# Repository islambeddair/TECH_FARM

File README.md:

# TECH_FARMMoisture Sensor

General Overview:
Soil moisture sensor measure the volumetric water content in soil. Since the direct gravimetric measurement of free soil moisture requires removing, drying, and weighting of a sample, soil moisture sensors measure the volumetric water content indirectly by using some other property of the soil, such as electrical resistance, dielectric constant, or interaction with neutrons, as a proxy for the moisture content. The relation between the measured property and soil moisture must be calibrated and may vary depending on environmental factors such as soil type, temperature, or electric conductivity. Reflected microwave radiation is affected by the soil moisture and is used for remote sensing in hydrology and agriculture. Portable probe instruments can be used by farmers or gardeners.
Applications:
Agriculture:
Measuring soil moisture is important for agricultural applications to help farmers manage their irrigation systems more efficiently. Knowing the exact soil moisture conditions on their fields, not only are farmers able to generally use less water to grow a crop, they are also able to increase yields and the quality of the crop by improved management of soil moisture during critical plant growth stages.
Landscape irrigation:
In urban and suburban areas, landscapes and residential lawns are using soil moisture sensors to interface with an irrigation controller. Connecting a soil moisture sensor to a simple irrigation clock will convert it into a "smart" irrigation controller that prevents irrigation cycles when the soil is already wet, e.g. following a recent rainfall event.
Golf courses are using soil moisture sensors to increase the efficiency of their irrigation systems to prevent over-watering and leaching of fertilizers and other chemicals into the ground.
Research:
Soil moisture sensors are used in numerous research applications, e.g. in agricultural science and horticulture including irrigation planning, climate research, or environmental science including solute transport studies and as auxiliary sensors for soil respiration measurements.

	We will use moisture sensor in agricultural applications. 
Hardware Overview:
The Soil Moisture Sensor is pretty straightforward when it comes to hookup. You need to supply VCC and GND. We recommend not powering the sensor constantly to prevent oxidation of the probes (more on this in a bit). You will get a SIG out, which will be between almost VCC and GND, depending on the amount of water in the soil. The two probes are acting as a variable resistor – more water in the soil means better conductivity and results in a lower resistance and a higher SIG out. Your analog readings will vary depending on what voltage you use for Vcc as well as the resolution of your ADC pins.

First: design the moisture sensor by using EAGLE program.

•	EAGLE schematic for moisture sensor.

•	EAGLE board for moisture sensor.

Second:  made (PCB) for moisture sensor.
 
•	Moisture sensor

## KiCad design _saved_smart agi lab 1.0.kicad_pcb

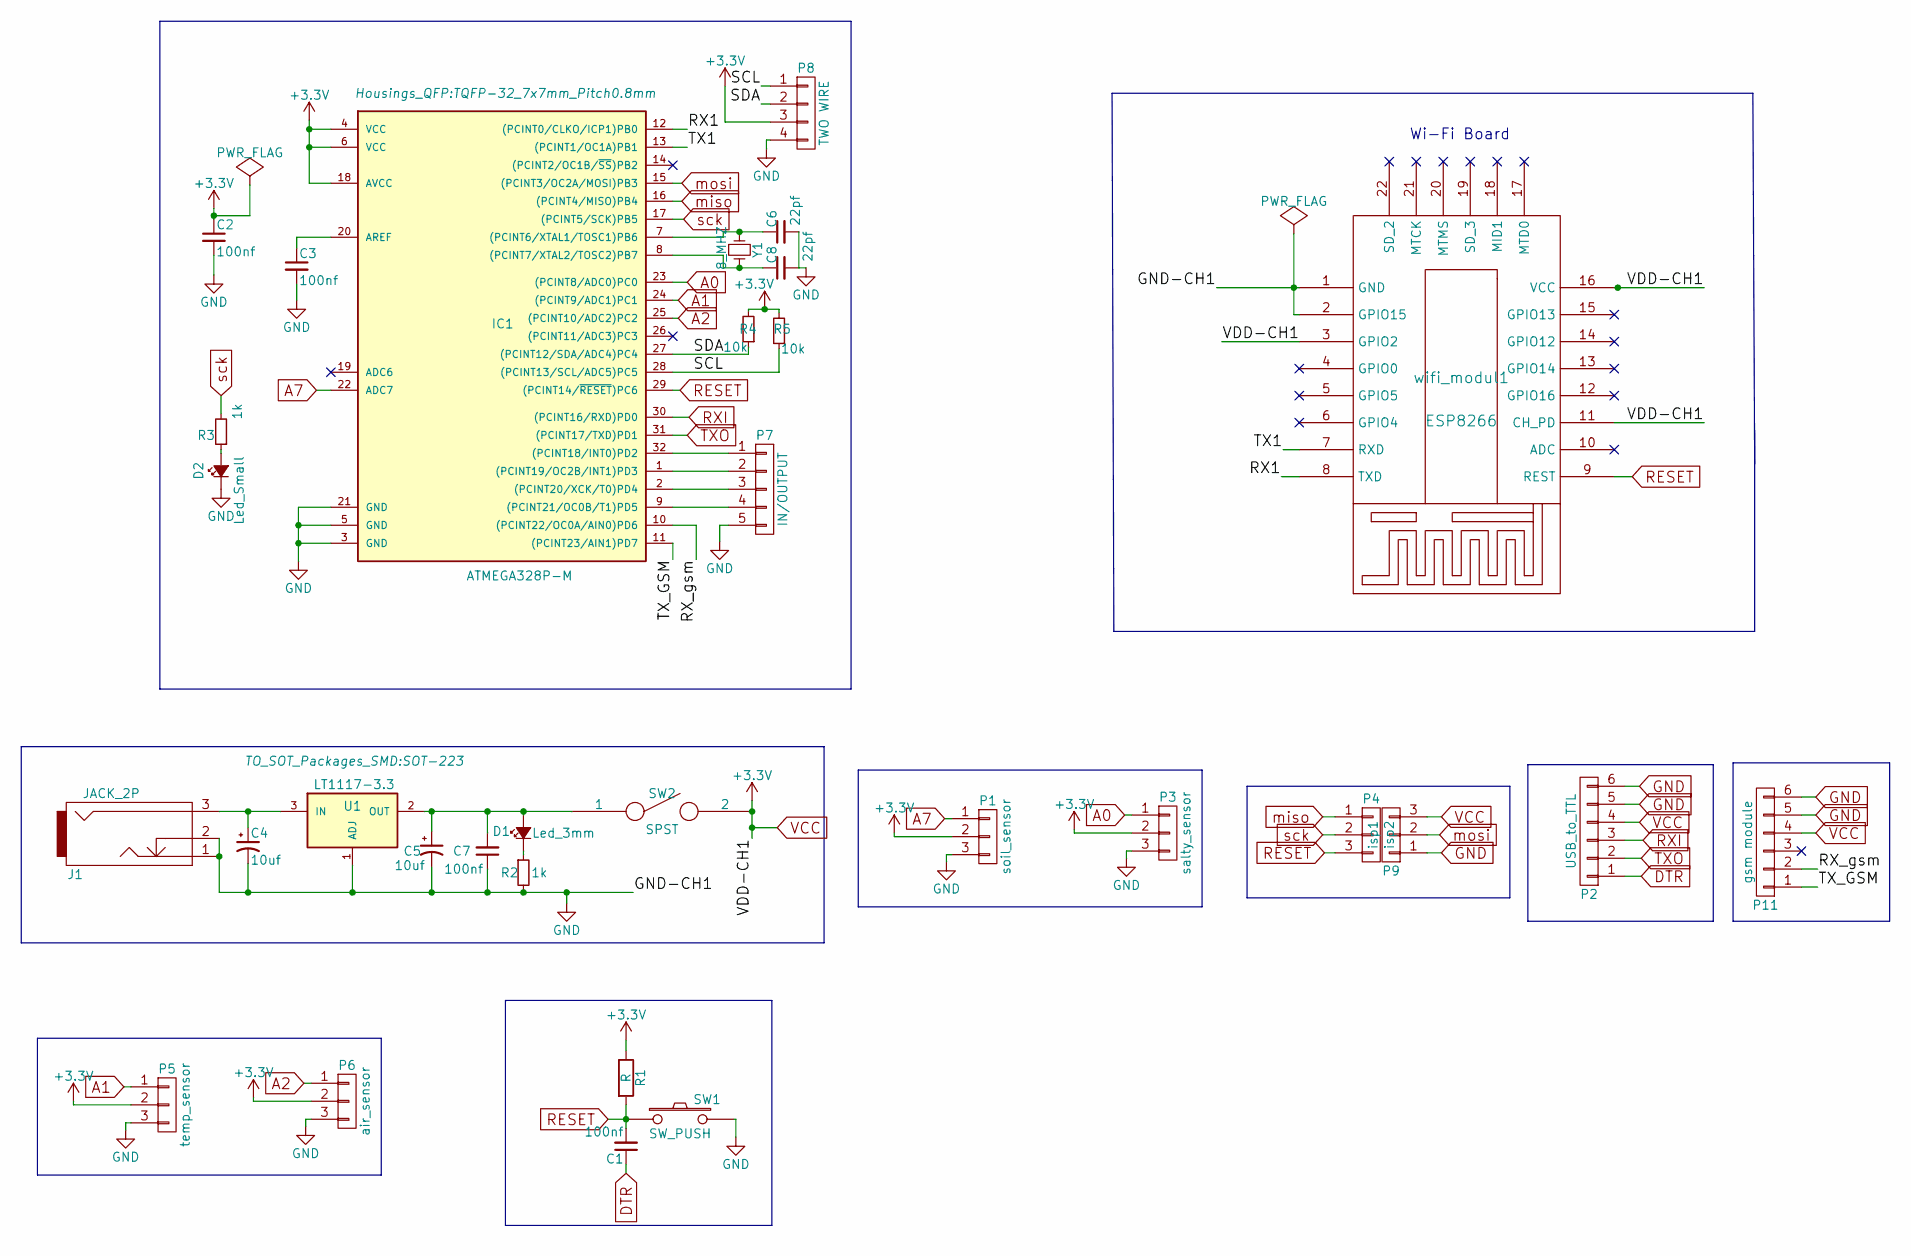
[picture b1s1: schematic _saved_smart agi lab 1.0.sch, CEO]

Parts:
C1: 100nf; C_Disc_D7.0mm_W2.5mm_P5.00mm
C2, C3, C7: 100nf; C_1206_HandSoldering
C4, C5: 10uf; C_1206_HandSoldering
C6, C8: 22pf; C_Disc_D3.0mm_W2.0mm_P2.50mm
D1: Led_3mm; LED_D3.0mm
D2: Led_Small; LED_D3.0mm
IC1: ATMEGA328P-M; TQFP-32_7x7mm_Pitch0.8mm
J1: JACK_2P; BARREL_JACK
P1: soil_sensor; AK300-3
P2: USB_to_TTL; Pin_Header_Straight_1x06_Pitch2.54mm
P3: salty_sensor; AK300-3
P4: isp2; Pin_Header_Straight_1x03_Pitch2.54mm
P5: temp_sensor; AK300-3
P6: air_sensor; AK300-3
P7: IN/OUTPUT; Pin_Header_Straight_1x05_Pitch2.54mm
P8: TWO WIRE; Pin_Header_Straight_1x04_Pitch2.54mm
P9: isp1; Pin_Header_Straight_1x03_Pitch2.54mm
P11: gsm module; Pin_Header_Straight_1x06_Pitch2.54mm
R1: R; R_1206_HandSoldering
R2, R3: 1k; R_1206_HandSoldering
R4, R5: 10k; R_1206_HandSoldering
SW1: SW_PUSH; SW_PUSH_6mm_h4.3mm
SW2: SPST; SW_PUSH_x2
U1: LT1117-3.3; SOT-223
Y1: 8_MHZ; Resonator-2pin_w7.0mm_h2.5mm
wifi_modul1: ESP8266; esp12

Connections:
/RX1: IC1.12 ((PCINT0/CLKO/ICP1)PB0), wifi_modul1.8 (TXD)
/RX_gsm: IC1.10 ((PCINT22/OC0A/AIN0)PD6), P11.2
/SCL: IC1.28 ((PCINT13/SCL/ADC5)PC5), P8.1, R5.1
/SDA: IC1.27 ((PCINT12/SDA/ADC4)PC4), P8.2, R4.1
/TX1: IC1.13 ((PCINT1/OC1A)PB1), wifi_modul1.7 (RXD)
/TX_GSM: IC1.11 ((PCINT23/AIN1)PD7), P11.1
A0: IC1.23 ((PCINT8/ADC0)PC0), P3.1
A1: IC1.24 ((PCINT9/ADC1)PC1), P5.1
A2: IC1.25 ((PCINT10/ADC2)PC2), P6.1
A7: IC1.22 (ADC7), P1.1
DTR: C1.1, P2.1
GND: C2.2, C3.2, C4.2, C5.2, C6.2, C7.1, C8.2, D2.1 (K), IC1.3 (GND), IC1.5 (GND), IC1.21 (GND), J1.1, J1.2, P1.3, P2.5, P2.6, P3.3, P5.3, P6.3, P7.5, P8.4, P9.1, P11.5, P11.6, R2.2, SW1.2, U1.1 (ADJ), wifi_modul1.1 (GND), wifi_modul1.2 (GPIO15)
unnamed: C3.1, IC1.20 (AREF)
unnamed: C4.1, J1.3, U1.3 (IN)
unnamed: C5.1, C7.2, D1.2 (A), SW2.1, U1.2 (OUT)
unnamed: C6.1, IC1.7 ((PCINT6/XTAL1/TOSC1)PB6), Y1.1
unnamed: C8.1, IC1.8 ((PCINT7/XTAL2/TOSC2)PB7), Y1.2
unnamed: D1.1 (K), R2.1
unnamed: D2.2 (A), R3.1
unnamed: IC1.1 ((PCINT19/OC2B/INT1)PD3), P7.2
unnamed: IC1.2 ((PCINT20/XCK/T0)PD4), P7.3
unnamed: IC1.9 ((PCINT21/OC0B/T1)PD5), P7.4
unnamed: IC1.32 ((PCINT18/INT0)PD2), P7.1
RESET: C1.2, IC1.29 ((PCINT14/~RESET~)PC6), P4.3, R1.2, SW1.1, wifi_modul1.9 (REST)
RXI: IC1.30 ((PCINT16/RXD)PD0), P2.3
TXO: IC1.31 ((PCINT17/TXD)PD1), P2.2
VCC: C2.1, IC1.4 (VCC), IC1.6 (VCC), IC1.18 (AVCC), P1.2, P2.4, P3.2, P5.2, P6.2, P8.3, P9.3, P11.4, R1.1, R4.2, R5.2, SW2.2, wifi_modul1.3 (GPIO2), wifi_modul1.11 (CH_PD), wifi_modul1.16 (VCC)
miso: IC1.16 ((PCINT4/MISO)PB4), P4.1
mosi: IC1.15 ((PCINT3/OC2A/MOSI)PB3), P9.2
sck: IC1.17 ((PCINT5/SCK)PB5), P4.2, R3.2

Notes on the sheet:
Wi-Fi Board

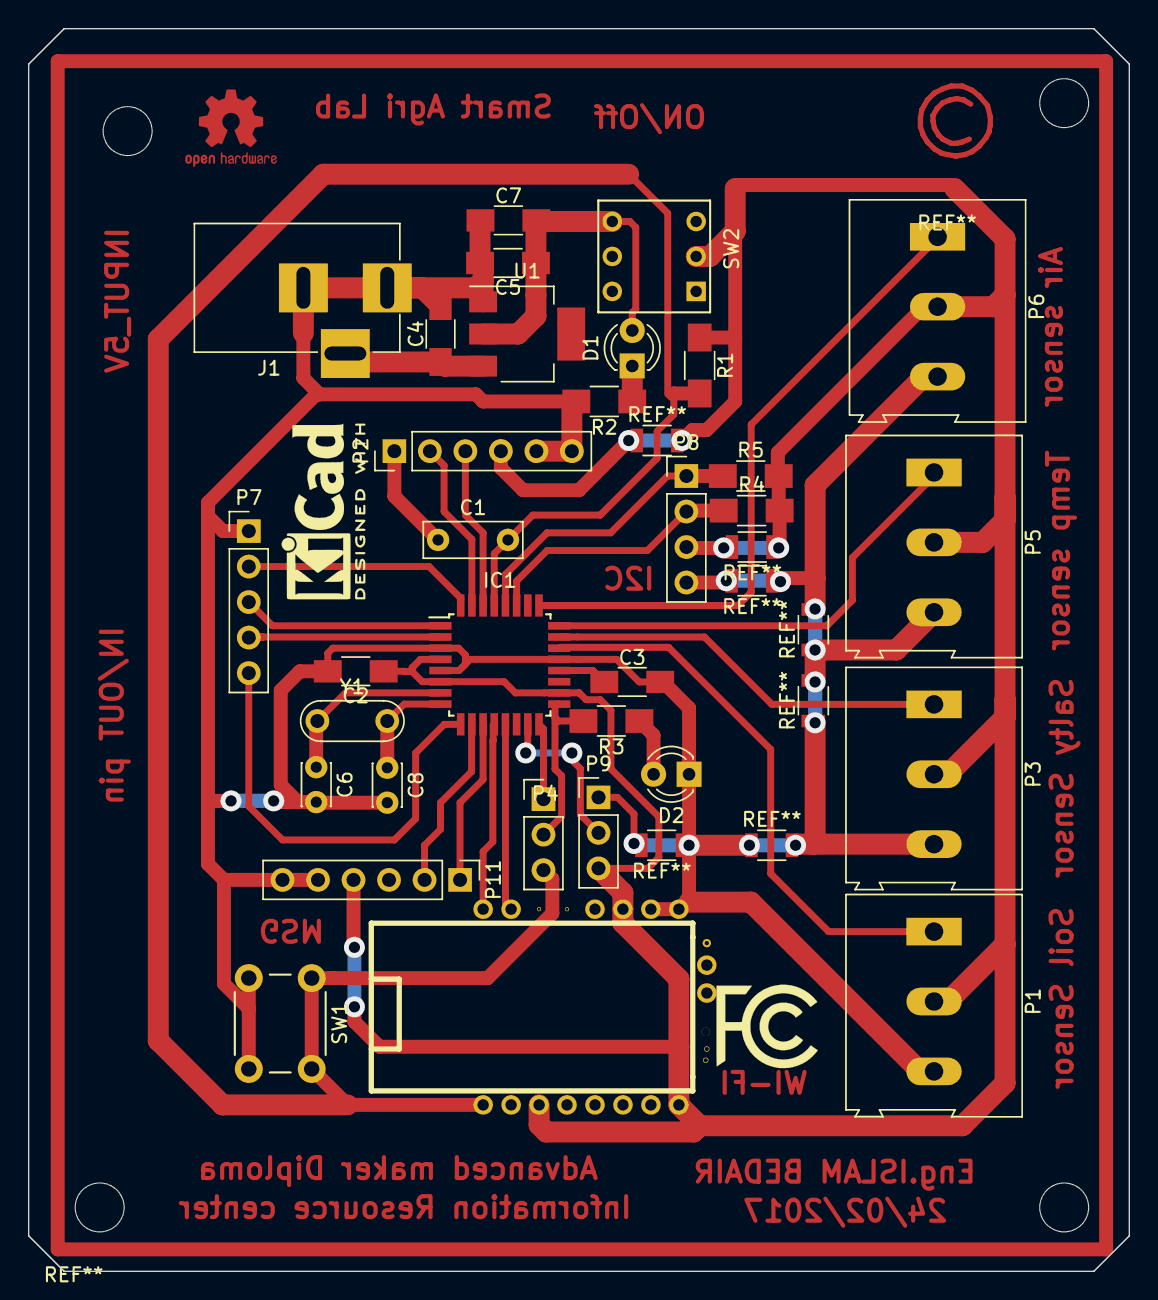
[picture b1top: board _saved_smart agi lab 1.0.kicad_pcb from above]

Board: 2 copper layers, 78.7 x 88.9 mm, 32 parts (0 on the bottom side), 30 nets.
